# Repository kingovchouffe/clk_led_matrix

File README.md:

# GNSS LED Matrix Clock Hardware

This repository contains KiCad hardware designs for a GNSS-oriented clock and LED matrix display. The primary design combines an STM32C0-series controller with an ATGM336H GNSS receiver; separate files capture a CH32V003-based 5x7 display design.

## Designs

### Main clock controller

The root KiCad project (`clk_led_matrix`) contains the main schematic, PCB layout, and an STM32CubeMX configuration. The schematic includes:

- An STM32C0-series MCU and ATGM336H-5N31 GNSS module.
- GNSS UART and I2C signal connections, plus USB 2.0 over a USB-C receptacle.
- Power circuitry, a reset switch, and a 2x3 debug/programming header.
- A four-layer PCB layout.

The `.ioc` file configures RTC, USB device, two I2C peripherals, and two UART peripherals. It is MCU configuration metadata, not firmware source code.

### CH32 LED display design

The `ch32_led/` directory contains a separate two-layer KiCad project built around a CH32V003 and a Lite-On LTP-305G green 5x7 dot-matrix display. Its schematic also includes a three-position DIP switch, address-selection signals, and a six-pin connector.

`5x7_MCU_Block.kicad_sch` is a standalone schematic for the CH32V003/display circuit, useful as a reference or reusable block. It is not a hierarchical sheet currently included in the root schematic.

## Repository contents

| Path | Description |
| --- | --- |
| `clk_led_matrix.kicad_pro` | Main KiCad project settings |
| `clk_led_matrix.kicad_sch` | Main clock-controller schematic |
| `clk_led_matrix.kicad_pcb` | Main four-layer PCB layout |
| `clk_led_matrix.ioc` | STM32CubeMX configuration for the main MCU |
| `ch32_led/` | Separate CH32V003 5x7 display schematic and PCB project |
| `5x7_MCU_Block.kicad_sch` | Standalone CH32V003 and 5x7 display schematic block |
| `fp-lib-table` | KiCad footprint library table |

## Opening the designs

Open `clk_led_matrix.kicad_pro` in KiCad to work on the main design. Open `ch32_led/ch32_led.kicad_pro` for the CH32 display board. The design files use KiCad 10-era file formats; older KiCad versions may not open them correctly.

The repository currently contains hardware design files, not embedded application source, generated firmware, a bill of materials, or fabrication exports. No firmware build or flashing procedure is defined here.

## Design note

Before ordering parts for the main controller, verify the exact STM32 package: the schematic symbol is named `STM32C071KBUx`, while `clk_led_matrix.ioc` identifies `STM32C071KBT6`. Confirm that the schematic, footprint, PCB, and MCU configuration all target the intended orderable part.

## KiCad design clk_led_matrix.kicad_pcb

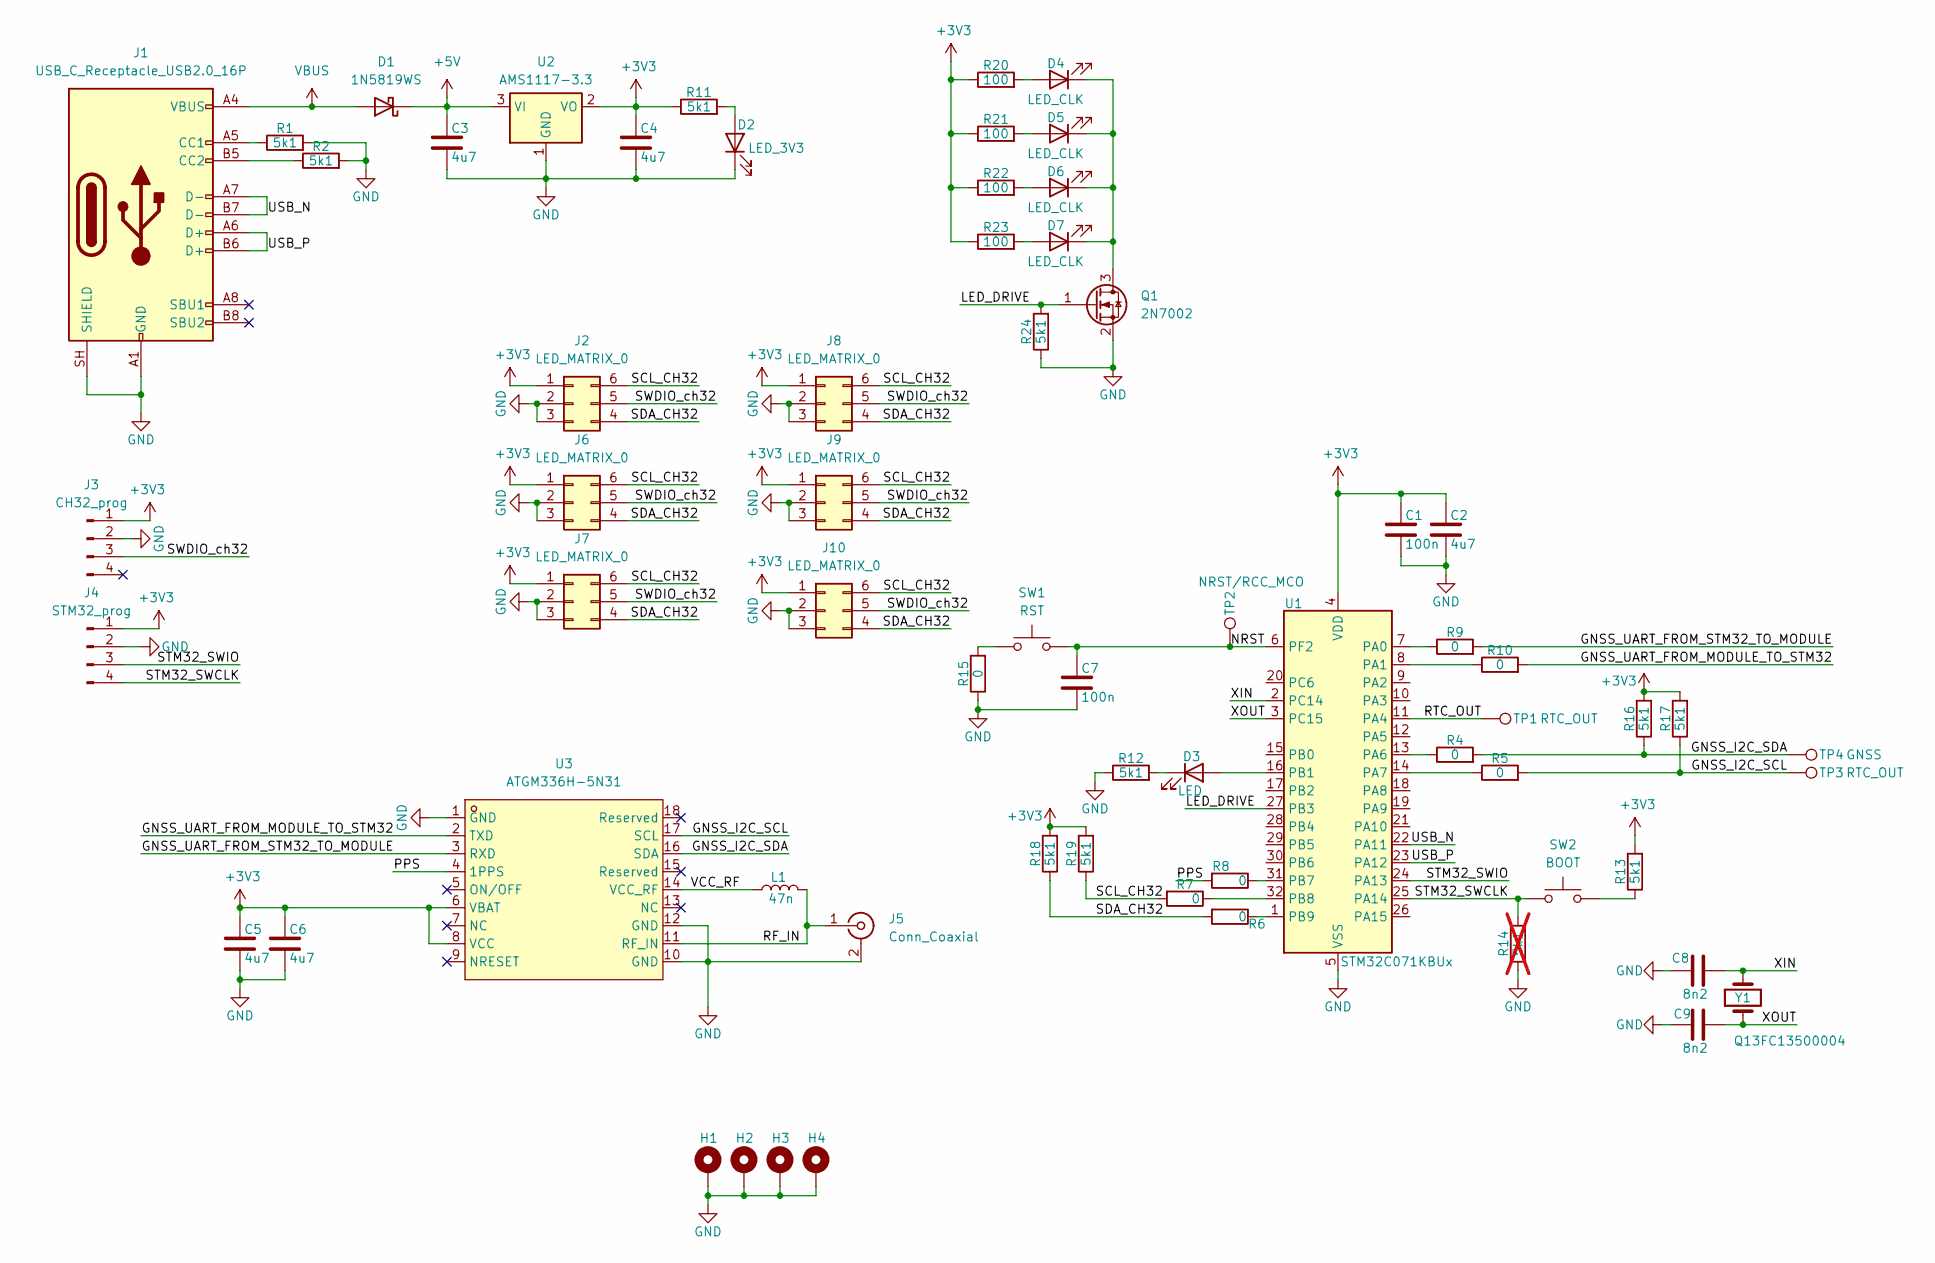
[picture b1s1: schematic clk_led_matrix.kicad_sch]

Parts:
C1, C7: 100n; C_0603_1608Metric
C2, C3, C4, C5, C6: 4u7; C_0603_1608Metric
C8, C9: 8n2; C_0603_1608Metric
D1: 1N5819WS; D_SOD-323
D2: LED_3V3; LED_0805_2012Metric
D3: LED; LED_0805_2012Metric
D4, D5, D6, D7: LED_CLK; LED_0805_2012Metric
H1, H2, H3, H4: MountingHole_Pad; MountingHole_3.2mm_M3_Pad_Via
J1: USB_C_Receptacle_USB2.0_16P; USB-C-TH_SHOUHAN_TYPE-C-14PLC-H10.0
J2, J6, J7, J8, J9, J10: LED_MATRIX_0; PinHeader_2x03_P1.27mm_Vertical
J3: CH32_prog; PinHeader_1x04_P1.27mm_Vertical
J4: STM32_prog; PinHeader_1x04_P1.27mm_Vertical
J5: Conn_Coaxial; U.FL_Molex_MCRF_73412-0110_Vertical
L1: 47n; L_0603_1608Metric
Q1: 2N7002; SOT-23; LCSC C8545
R1, R2, R11, R12, R13, R16, R17, R18, R19, R24: 5k1; R_0603_1608Metric
R4, R5, R6, R7, R8, R9, R10, R15: 0; R_0603_1608Metric
R14: 5k1; R_0603_1608Metric; not fitted
R20, R21, R22, R23: 100; R_0603_1608Metric
SW1: RST; SW_SPST_TS-1088-xR020; LCSC C720477
SW2: BOOT; SW_SPST_TS-1088-xR020; LCSC C720477
TP1, TP3: RTC_OUT; TestPoint_Pad_D1.0mm
TP2: NRST/RCC_MCO; TestPoint_Pad_D1.0mm
TP4: GNSS; TestPoint_Pad_D1.0mm
U1: STM32C071KBUx; QFN-32-1EP_5x5mm_P0.5mm_EP3.45x3.45mm
U2: AMS1117-3.3; SOT-223-3_TabPin2
U3: ATGM336H-5N31; GPSM-SMD_ATGM336H-TR; MPN ATGM336H-5N31; LCSC C90770
Y1: Q13FC13500004; Crystal_SMD_3215-2Pin_3.2x1.5mm; LCSC C32346

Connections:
+3V3: C1.1, C2.1, C4.1, C5.1, C6.1, J2.1, J3.1, J4.1, J6.1, J7.1, J8.1, J9.1, J10.1, R11.1, R13.2, R16.2, R17.2, R18.2, R19.2, R20.1, R21.1, R22.1, R23.1, U1.4 (VDD), U2.2 (VO), U3.6 (VBAT), U3.8 (VCC)
+5V: C3.1, D1.1 (K), U2.3 (VI)
/GNSS_I2C_SCL: R5.2, R17.1, TP3.1, U3.17 (SCL)
/GNSS_I2C_SDA: R4.2, R16.1, TP4.1, U3.16 (SDA)
/GNSS_UART_FROM_MODULE_TO_STM32: R10.2, U3.2 (TXD)
/GNSS_UART_FROM_STM32_TO_MODULE: R9.2, U3.3 (RXD)
/LED_DRIVE: Q1.1 (G), R24.2, U1.27 (PB3)
/NRST: C7.1, SW1.2, TP2.1 (1_1), U1.6 (PF2)
/PPS: R8.2, U3.4 (1PPS)
/RF_IN: J5.1 (In), L1.2, U3.11 (RF_IN)
/RTC_OUT: TP1.1 (1_1), U1.11 (PA4)
/SCL_CH32: J2.6, J6.6, J7.6, J8.6, J9.6, J10.6, R7.2, R19.1
/SDA_CH32: J2.4, J6.4, J7.4, J8.4, J9.4, J10.4, R6.2, R18.1
/STM32_SWCLK: J4.4, R14.2, SW2.1, U1.25 (PA14)
/STM32_SWIO: J4.3, U1.24 (PA13)
/SWDIO_ch32: J2.5, J3.3, J6.5, J7.5, J8.5, J9.5, J10.5
/USB_N: J1.A7 (D-), J1.B7 (D-), U1.22 (PA11)
/USB_P: J1.A6 (D+), J1.B6 (D+), U1.23 (PA12)
/VCC_RF: L1.1, U3.14 (VCC_RF)
/XIN: C8.1, U1.2 (PC14), Y1.2
/XOUT: C9.1, U1.3 (PC15), Y1.1
GND: C1.2, C2.2, C3.2, C4.2, C5.2, C6.2, C7.2, C8.2, C9.2, D2.1 (K), H1.1 (1_1), H2.1 (1_1), H3.1 (1_1), H4.1 (1_1), J1.A1 (GND), J1.A12 (GND), J1.B1 (GND), J1.B12 (GND), J1.SH (SHIELD), J2.2, J2.3, J3.2, J4.2, J5.2 (Ext), J6.2, J6.3, J7.2, J7.3, J8.2, J8.3, J9.2, J9.3, J10.2, J10.3, Q1.2 (S), R1.2, R2.2, R12.1, R14.1, R15.1, R24.1, U1.5 (VSS), U1.33 (VSS), U2.1 (GND), U3.1 (GND), U3.10 (GND), U3.12 (GND)
unnamed: D2.2 (A), R11.2
unnamed: D3.2 (A), U1.16 (PB1)
unnamed: D3.1 (K), R12.2
unnamed: D4.2 (A), R20.2
unnamed: D4.1 (K), D5.1 (K), D6.1 (K), D7.1 (K), Q1.3 (D)
unnamed: D5.2 (A), R21.2
unnamed: D6.2 (A), R22.2
unnamed: D7.2 (A), R23.2
unnamed: J1.A5 (CC1), R1.1
unnamed: J1.B5 (CC2), R2.1
unnamed: R13.1, SW2.2
unnamed: R15.2, SW1.1
unnamed: R9.1, U1.7 (PA0)
unnamed: R10.1, U1.8 (PA1)
unnamed: R4.1, U1.13 (PA6)
unnamed: R5.1, U1.14 (PA7)
unnamed: R8.1, U1.31 (PB7)
unnamed: R7.1, U1.32 (PB8)
unnamed: R6.1, U1.1 (PB9)
VBUS: D1.2 (A), J1.A4 (VBUS), J1.A9 (VBUS), J1.B4 (VBUS), J1.B9 (VBUS)

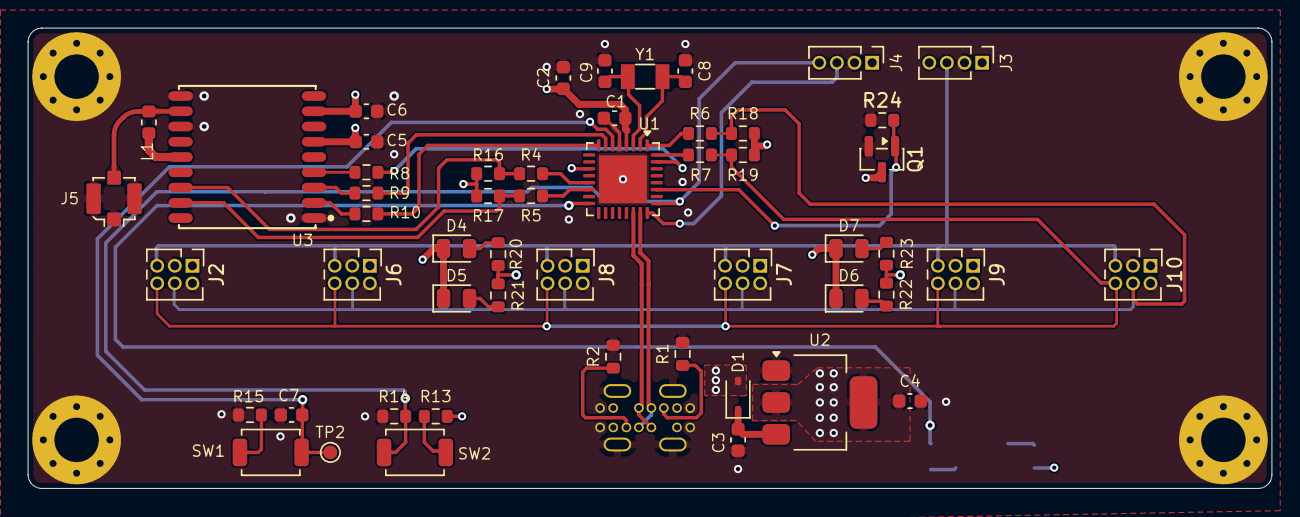
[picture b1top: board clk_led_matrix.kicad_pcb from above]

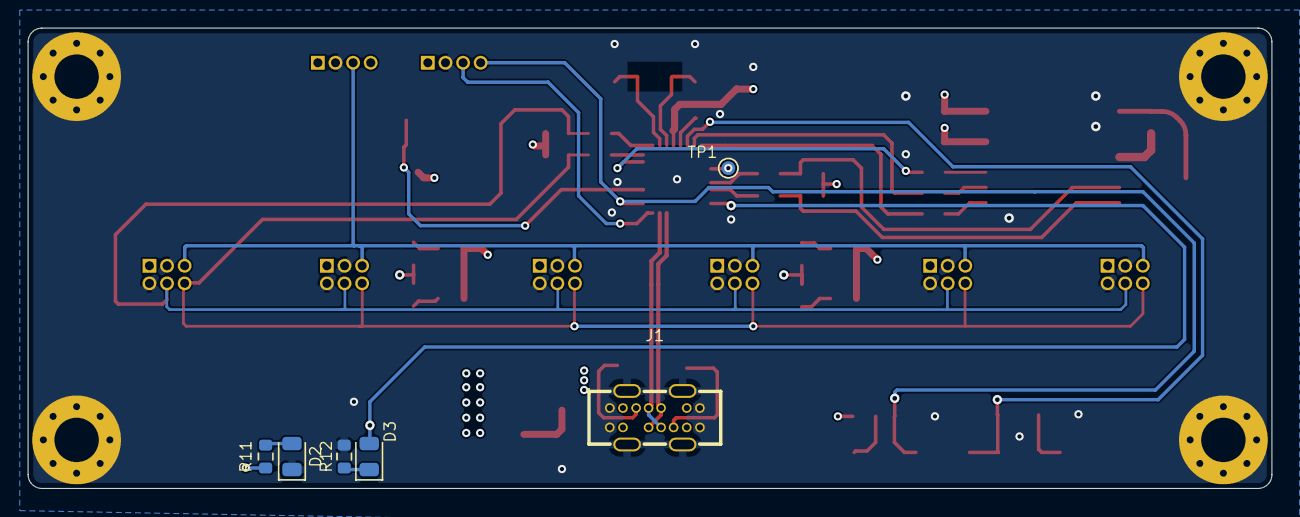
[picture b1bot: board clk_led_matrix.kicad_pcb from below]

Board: 4 copper layers, 89.7 x 33.2 mm, 63 parts (6 on the bottom side), 42 nets.

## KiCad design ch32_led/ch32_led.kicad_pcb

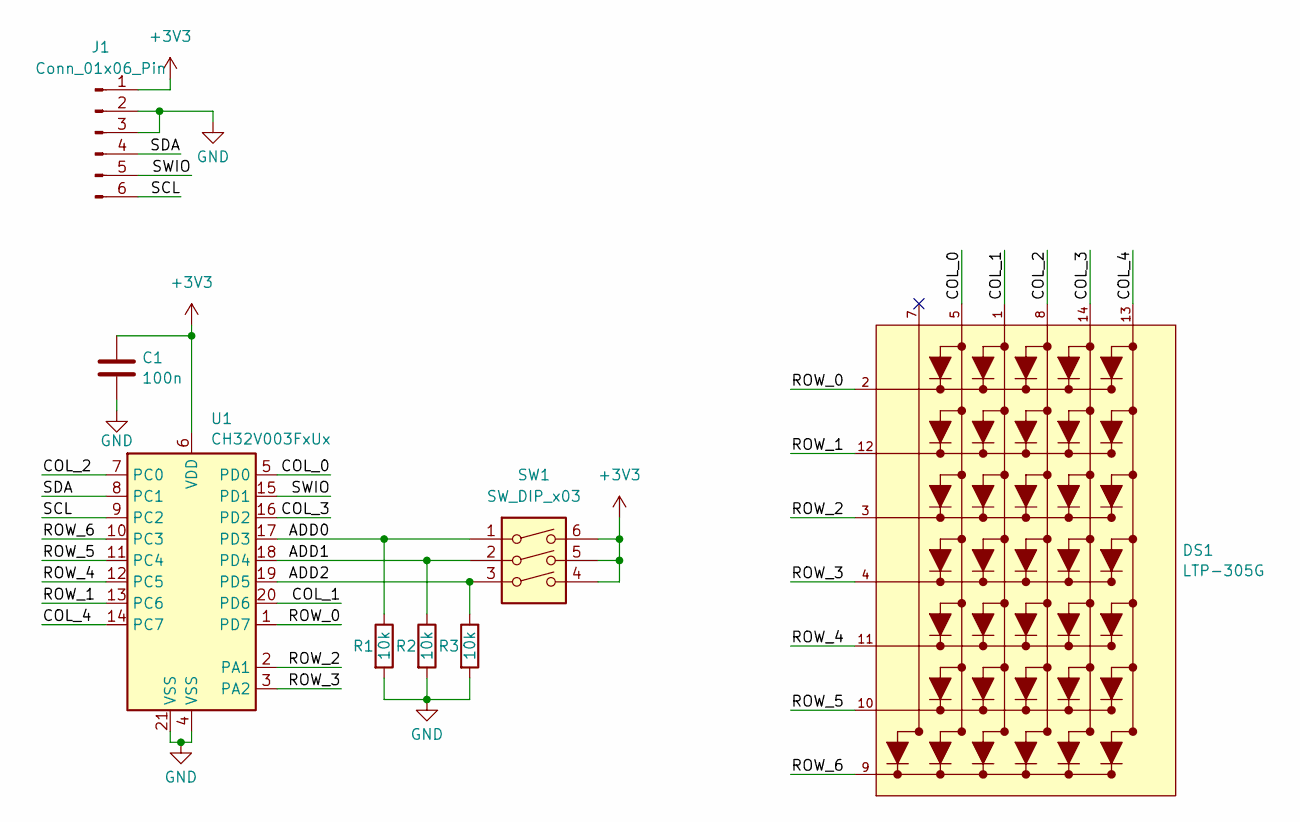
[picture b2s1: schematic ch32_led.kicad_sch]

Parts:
C1: 100n; C_0603_1608Metric
DS1: LTP-305G; DIP762W50P254L1875H400Q13; PARTREV A
J1: Conn_01x06_Pin; PinHeader_2x03_P1.27mm_Vertical_SMD
R1, R2, R3: 10k; R_0603_1608Metric
SW1: SW_DIP_x03; SW_DIP_SPSTx03_Slide_KingTek_DSHP03TS_W7.62mm_P1.27mm
U1: CH32V003FxUx; QFN-20-1EP_3x3mm_P0.4mm_EP1.65x1.65mm

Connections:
+3V3: C1.2, J1.1, SW1.4, SW1.5, SW1.6, U1.6 (VDD)
/ADD0: R1.1, SW1.1, U1.17 (PD3)
/ADD1: R2.1, SW1.2, U1.18 (PD4)
/ADD2: R3.1, SW1.3, U1.19 (PD5)
/COL_0: DS1.5, U1.5 (PD0)
/COL_1: DS1.1, U1.20 (PD6)
/COL_2: DS1.8, U1.7 (PC0)
/COL_3: DS1.14, U1.16 (PD2)
/COL_4: DS1.13, U1.14 (PC7)
/ROW_0: DS1.2, U1.1 (PD7)
/ROW_1: DS1.12, U1.13 (PC6)
/ROW_2: DS1.3, U1.2 (PA1)
/ROW_3: DS1.4, U1.3 (PA2)
/ROW_4: DS1.11, U1.12 (PC5)
/ROW_5: DS1.10, U1.11 (PC4)
/ROW_6: DS1.9, U1.10 (PC3)
/SCL: J1.6, U1.9 (PC2)
/SDA: J1.4, U1.8 (PC1)
/SWIO: J1.5, U1.15 (PD1)
GND: C1.1, J1.2, J1.3, R1.2, R2.2, R3.2, U1.4 (VSS), U1.21 (VSS)

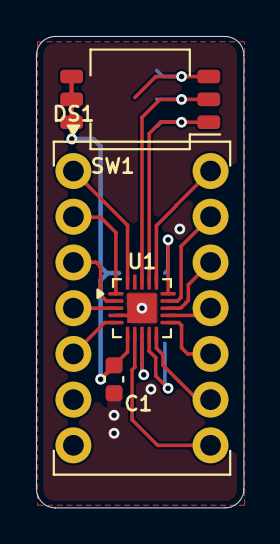
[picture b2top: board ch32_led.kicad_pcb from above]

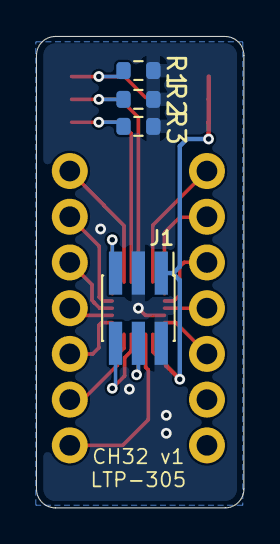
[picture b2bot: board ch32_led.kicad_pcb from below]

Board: 2 copper layers, 11.5 x 26.2 mm, 8 parts (4 on the bottom side), 20 nets.

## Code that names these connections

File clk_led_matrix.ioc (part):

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Mcu.Name=STM32C071KBTx
Mcu.Package=LQFP32_GP
Mcu.UserName=STM32C071KBTx
PA0.Mode=Asynchronous
PA0.Signal=USART1_TX
PA1.Mode=Asynchronous
PA1.Signal=USART1_RX
PA11\ [PA9].Mode=Device
PA11\ [PA9].Signal=USB_DM
PA12\ [PA10].Mode=Device
PA12\ [PA10].Signal=USB_DP
PA13.Mode=Serial_Wire
PA13.Signal=DEBUG_SWDIO
PA14-BOOT0.Mode=Serial_Wire
PA14-BOOT0.Signal=DEBUG_SWCLK
PA2.GPIOParameters=GPIO_Label
PA2.GPIO_Label=UART2_TX+LSCO_out
PA2.Mode=Asynchronous
PA2.Signal=USART2_TX
PA3.Mode=Asynchronous
PA3.Signal=USART2_RX
PA4.Mode=Calibration_1Hz
PA4.Signal=RTC_OUT1
PA6.Mode=I2C
PA6.Signal=I2C2_SDA
PA7.Mode=I2C
PA7.Signal=I2C2_SCL
PB7.Mode=Reference_Clock_Detection_Activate
PB7.Signal=RTC_REFIN
PB8.Mode=I2C
PB8.Signal=I2C1_SCL
PB9.Mode=I2C
PB9.Signal=I2C1_SDA
PC14-OSCX_IN(PC14).Mode=LSE-External-Oscillator
PC14-OSCX_IN(PC14).Signal=RCC_OSCX_IN
PC15-OSCX_OUT(PC15).Mode=LSE-External-Oscillator
PC15-OSCX_OUT(PC15).Signal=RCC_OSCX_OUT
PF2-NRST.Mode=Clock-out
PF2-NRST.Signal=RCC_MCO
RCC.SYSCLKFreq_VALUE=48000000
board=custom
